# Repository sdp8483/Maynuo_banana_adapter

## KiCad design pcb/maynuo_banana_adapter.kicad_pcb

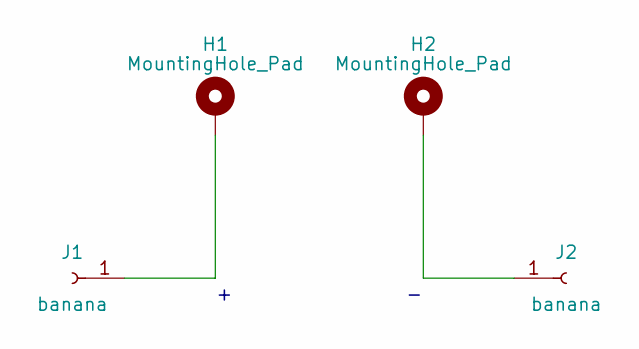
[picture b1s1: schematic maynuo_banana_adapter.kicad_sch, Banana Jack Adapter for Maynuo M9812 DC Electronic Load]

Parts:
H1, H2: MountingHole_Pad; MountingHole_6.4mm_M6_DIN965_Pad
J1: banana; CT3151; MPN CT3151V1-2
J2: banana; CT3151; MPN CT3151V1-0

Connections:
unnamed: H1.1, J1.1
unnamed: H2.1, J2.1

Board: 2 copper layers, 4 parts (0 on the bottom side), 2 nets, no tracks yet.

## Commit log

2023-04-26 Create fp-lib-table
2023-04-26 export gerber
2023-04-26 create gcode
